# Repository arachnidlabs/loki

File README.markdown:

Loki
====

Loki is a flexible development platform based on Cypress's PSoC 5 line of processors.

For much more about Loki, check out the [Arachnid Labs Blog](http://www.arachnidlabs.com/)

All the Loki source and schematics are open hardware and OSS, and licensed under the [BSD 2-clause license](http://opensource.org/licenses/BSD-2-Clause). Reuse and remix as you see fit!

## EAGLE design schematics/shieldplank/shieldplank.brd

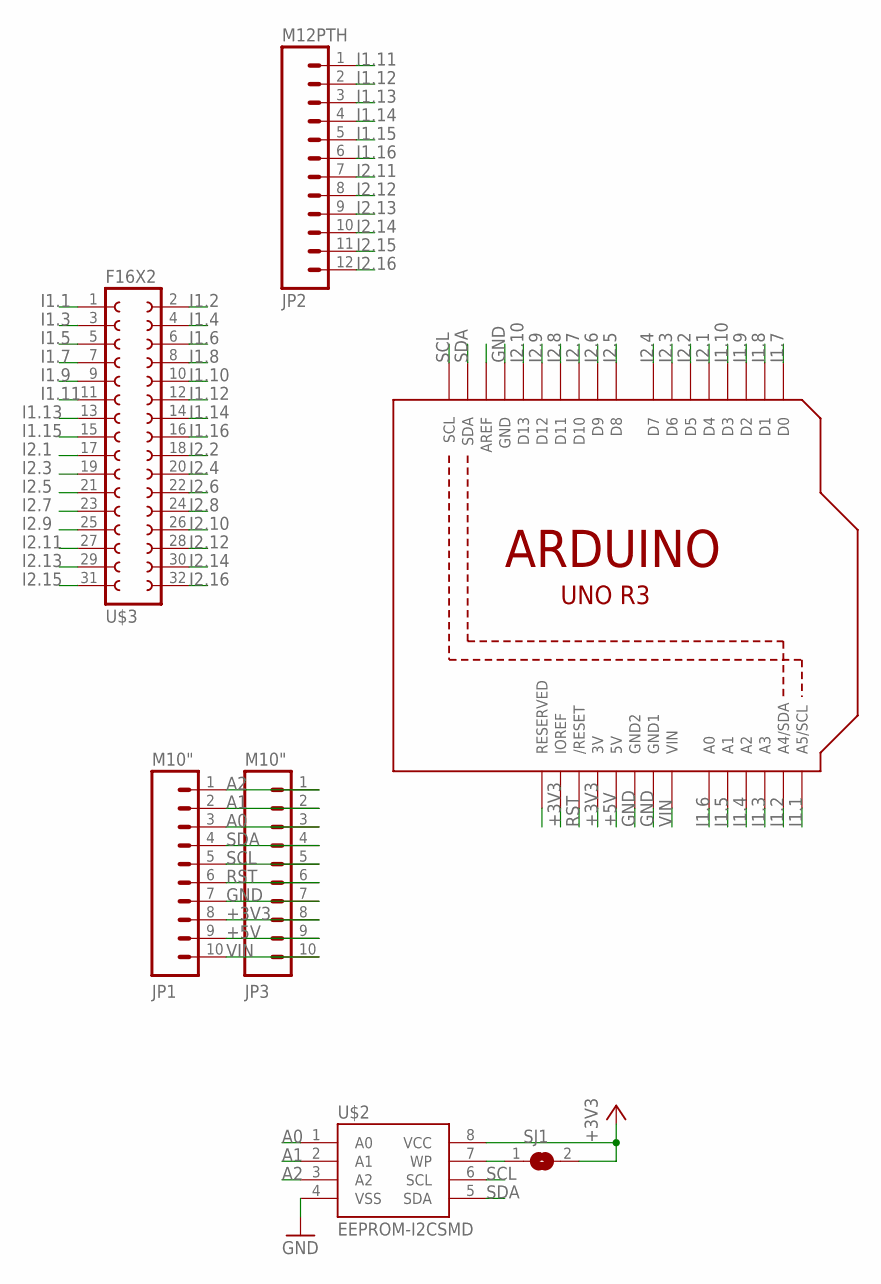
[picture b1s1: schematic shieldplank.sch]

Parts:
JP1, JP3: M10"; 1X10
JP2: M12PTH; 1X12
SJ1: SJ
U1: ARDUINOR3-BPLACE
U$2: EEPROM-I2CSMD; SO08
U$3: F16X2; FE16-2

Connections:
+3V3: JP1.8, JP3.8, SJ1.2, U1.3V, U1.IOREF, U$2.8 (VCC)
+5V: JP1.9, JP3.9, U1.5V
A0: JP1.3, JP3.3, U$2.1 (A0)
A1: JP1.2, JP3.2, U$2.2 (A1)
A2: JP1.1, JP3.1, U$2.3 (A2)
GND: JP1.7, JP3.7, U1.GND, U1.GND1, U1.GND2, U$2.4 (VSS)
I1.1: U1.A5 (A5/SCL), U$3.1
I1.2: U1.A4 (A4/SDA), U$3.2
I1.3: U1.A3, U$3.3
I1.4: U1.A2, U$3.4
I1.5: U1.A1, U$3.5
I1.6: U1.A0, U$3.6
I1.7: U1.D0, U$3.7
I1.8: U1.D1, U$3.8
I1.9: U1.D2, U$3.9
I1.10: U1.D3, U$3.10
I1.11: JP2.1, U$3.11
I1.12: JP2.2, U$3.12
I1.13: JP2.3, U$3.13
I1.14: JP2.4, U$3.14
I1.15: JP2.5, U$3.15
I1.16: JP2.6, U$3.16
I2.1: U1.D4, U$3.17
I2.2: U1.D5, U$3.18
I2.3: U1.D6, U$3.19
I2.4: U1.D7, U$3.20
I2.5: U1.D8, U$3.21
I2.6: U1.D9, U$3.22
I2.7: U1.D10, U$3.23
I2.8: U1.D11, U$3.24
I2.9: U1.D12, U$3.25
I2.10: U1.D13, U$3.26
I2.11: JP2.7, U$3.27
I2.12: JP2.8, U$3.28
I2.13: JP2.9, U$3.29
I2.14: JP2.10, U$3.30
I2.15: JP2.11, U$3.31
I2.16: JP2.12, U$3.32
unnamed: SJ1.1, U$2.7 (WP)
RST: JP1.6, JP3.6, U1.RESET (/RESET)
SCL: JP1.5, JP3.5, U1.SCL, U$2.6 (SCL)
SDA: JP1.4, JP3.4, U1.SDA, U$2.5 (SDA)
VIN: JP1.10, JP3.10, U1.VIN

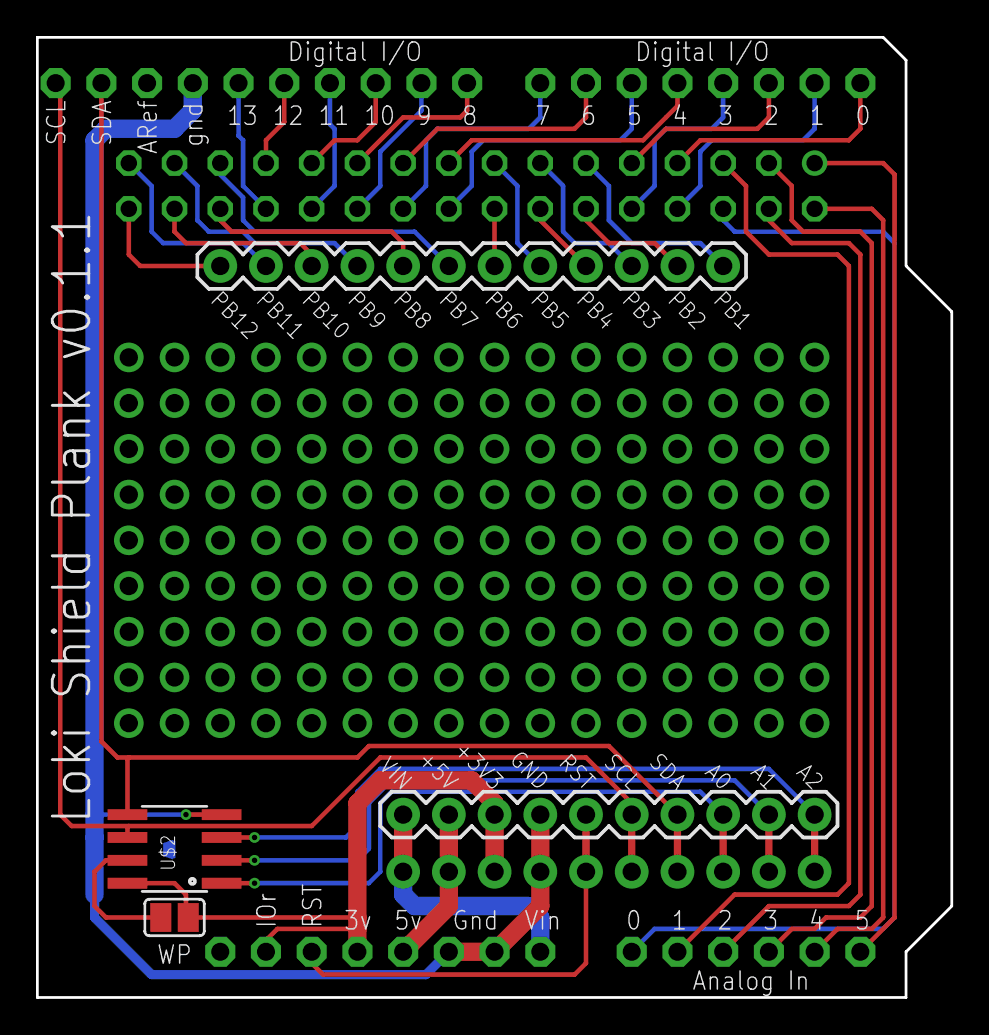
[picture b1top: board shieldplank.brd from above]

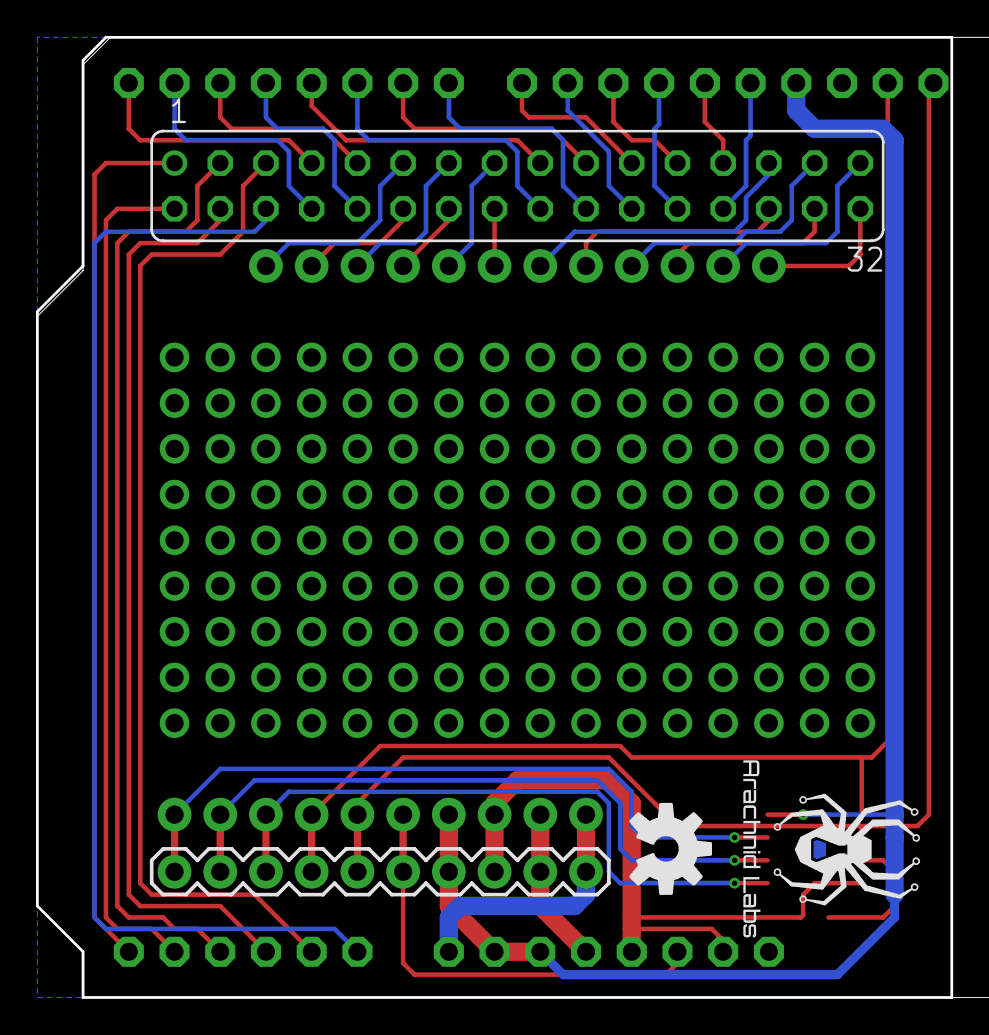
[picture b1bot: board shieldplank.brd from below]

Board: 2 copper layers, 50.8 x 53.3 mm, 9 parts (4 on the bottom side), 43 nets.

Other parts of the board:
U$1: ARACHNID_LABS_LOGO_SM
U$4: OSHW-LOGO-M

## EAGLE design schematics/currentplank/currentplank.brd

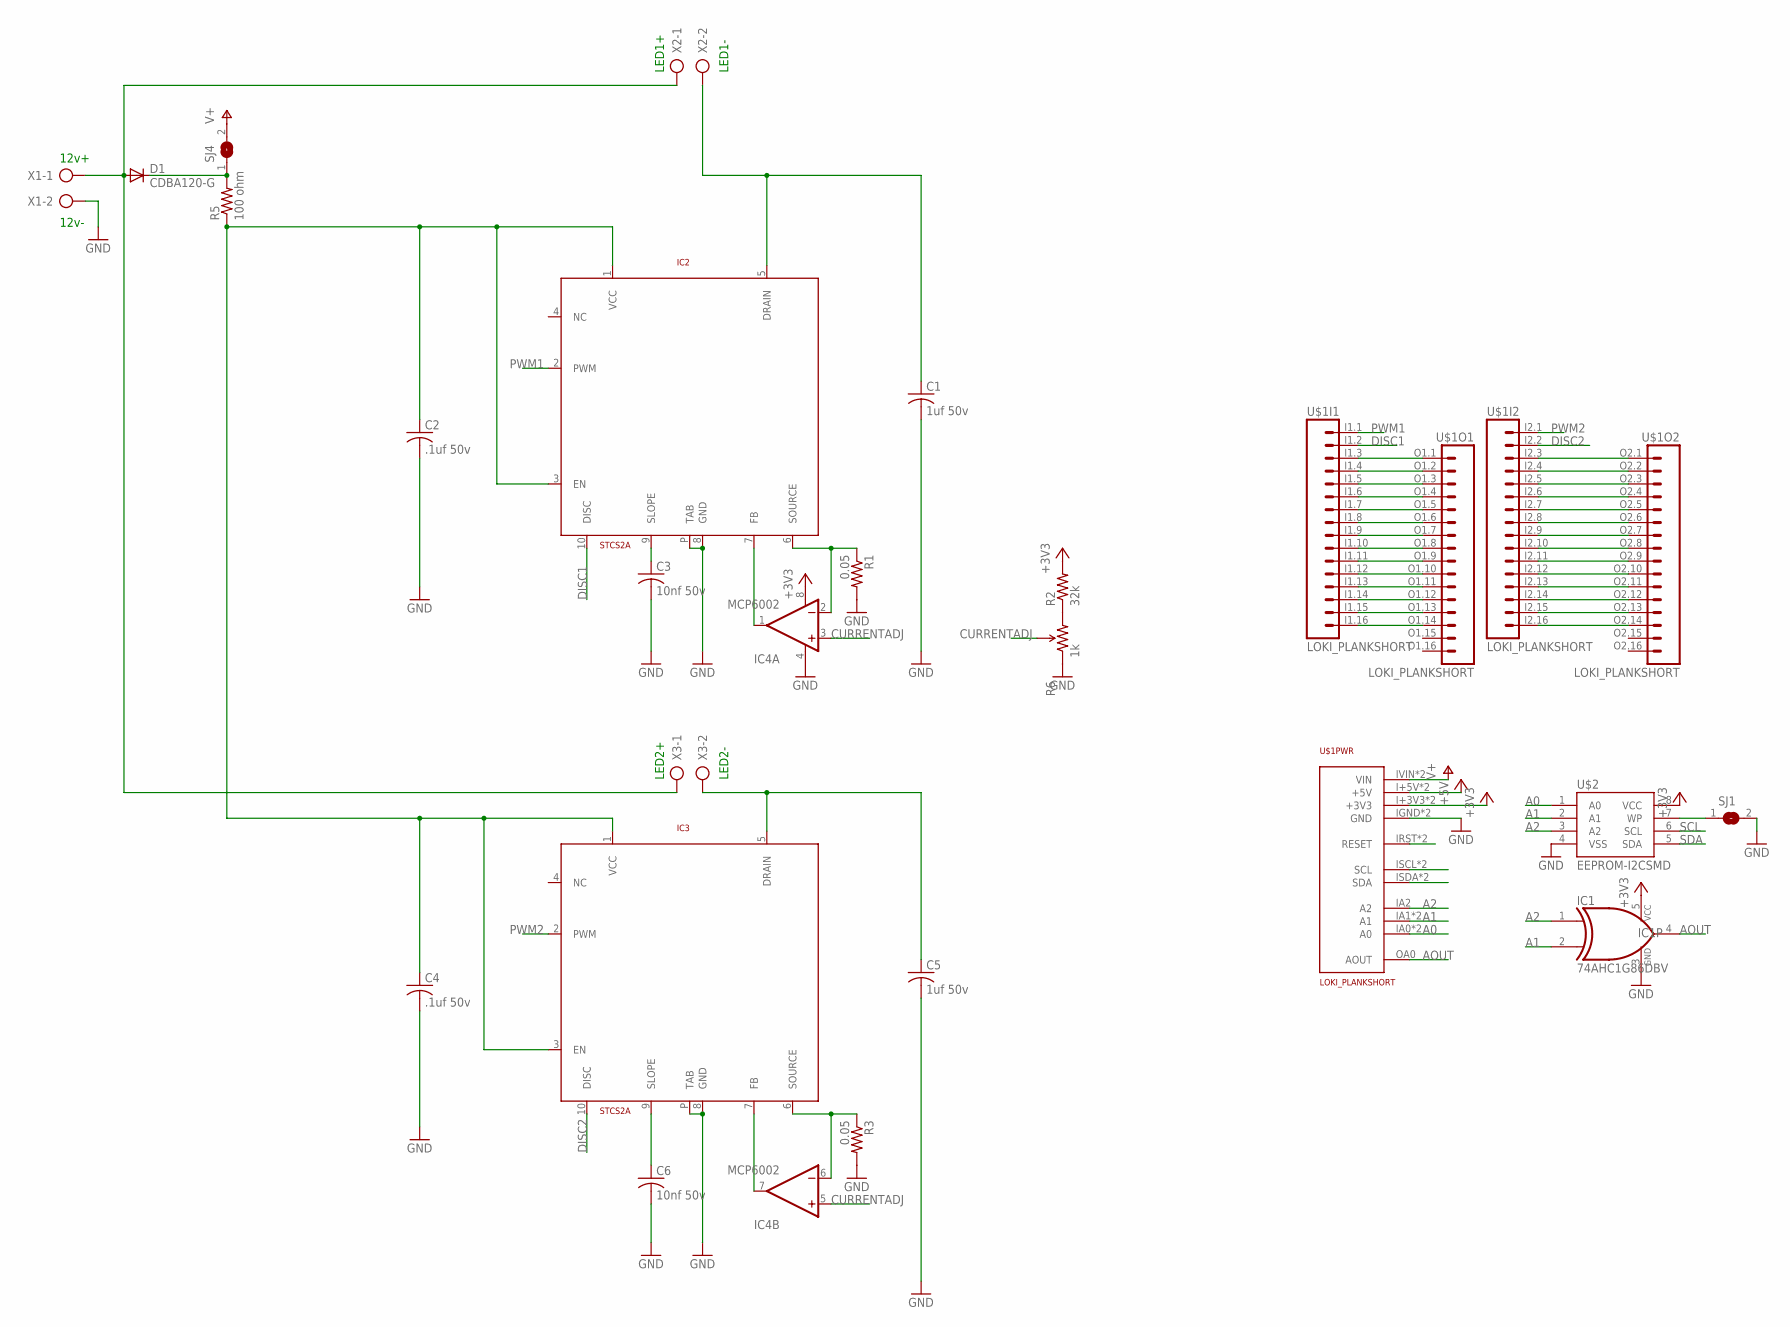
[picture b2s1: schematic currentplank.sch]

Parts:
C1, C5: 1uf 50v; C0805
C2, C4: .1uf 50v; C0805
C3, C6: 10nf 50v; C0805
D1: CDBA120-G; SMA-DIODE
IC1: 74AHC1G86DBV; SOT23-5
IC2, IC3: STCS2A; STCS2A_POWER-SO10
IC4: MCP6002; SO08
R1, R3: 0.05; 1206
R2: 32k; 0805
R5: 100 ohm; 0805
R6: 1k; TRIMPOT-3MM-2
SJ1, SJ4: SJ
U$1: LOKI_PLANKSHORT; PLANK_SHORT
U$2: EEPROM-I2CSMD; SO08
X1, X2, X3: AK500/2-H

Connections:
+3V3: IC1.5 (VCC), IC4.8 (V+), R2.2, U$1.I+3V3 (+3V3), U$1.O+3V3 (+3V3), U$2.8 (VCC)
+5V: U$1.I+5V (+5V), U$1.O+5V (+5V)
A0: U$1.IA0 (A0), U$1.OA1 (A0), U$2.1 (A0)
A1: IC1.2 (I1), U$1.IA1 (A1), U$1.OA2 (A1), U$2.2 (A1)
A2: IC1.1 (I0), U$1.IA2 (A2), U$2.3 (A2)
AOUT: IC1.4 (O), U$1.OA0 (AOUT)
CURRENTADJ: IC4.3 (+IN), IC4.5 (+IN), R6.2 (WIPER)
DISC1: IC2.10 (DISC), U$1.I1.2 (2)
DISC2: IC3.10 (DISC), U$1.I2.2 (2)
GND: C1.2, C2.2, C3.2, C4.2, C5.2, C6.2, IC1.3 (GND), IC2.8 (GND), IC2.P (TAB), IC3.8 (GND), IC3.P (TAB), IC4.4 (V-), R1.2, R3.2, R6.1 (CCW), SJ1.2, U$1.IGND (GND), U$1.OGND (GND), U$2.4 (VSS), X1.2
unnamed: U$1.I1.16 (16), U$1.O1.14 (14)
unnamed: U$1.I1.15 (15), U$1.O1.13 (13)
unnamed: U$1.I1.14 (14), U$1.O1.12 (12)
unnamed: U$1.I1.13 (13), U$1.O1.11 (11)
unnamed: U$1.I1.12 (12), U$1.O1.10 (10)
unnamed: U$1.I1.11 (11), U$1.O1.9 (9)
unnamed: U$1.I1.10 (10), U$1.O1.8 (8)
unnamed: U$1.I1.9 (9), U$1.O1.7 (7)
unnamed: U$1.I1.8 (8), U$1.O1.6 (6)
unnamed: U$1.I1.7 (7), U$1.O1.5 (5)
unnamed: U$1.I1.6 (6), U$1.O1.4 (4)
unnamed: U$1.I1.5 (5), U$1.O1.3 (3)
unnamed: U$1.I1.4 (4), U$1.O1.2 (2)
unnamed: U$1.I1.3 (3), U$1.O1.1 (1)
unnamed: U$1.I2.16 (16), U$1.O2.14 (14)
unnamed: U$1.I2.15 (15), U$1.O2.13 (13)
unnamed: U$1.I2.14 (14), U$1.O2.12 (12)
unnamed: U$1.I2.13 (13), U$1.O2.11 (11)
unnamed: U$1.I2.12 (12), U$1.O2.10 (10)
unnamed: U$1.I2.11 (11), U$1.O2.9 (9)
unnamed: U$1.I2.10 (10), U$1.O2.8 (8)
unnamed: U$1.I2.9 (9), U$1.O2.7 (7)
unnamed: U$1.I2.8 (8), U$1.O2.6 (6)
unnamed: U$1.I2.7 (7), U$1.O2.5 (5)
unnamed: U$1.I2.6 (6), U$1.O2.4 (4)
unnamed: U$1.I2.5 (5), U$1.O2.3 (3)
unnamed: U$1.I2.4 (4), U$1.O2.2 (2)
unnamed: U$1.I2.3 (3), U$1.O2.1 (1)
unnamed: IC2.6 (SOURCE), IC4.2 (-IN), R1.1
unnamed: IC2.7 (FB), IC4.1 (OUT)
unnamed: SJ1.1, U$2.7 (WP)
unnamed: U$1.IRST (RESET), U$1.ORST (RESET)
unnamed: D1.C, R5.2, SJ4.1
unnamed: C3.1, IC2.9 (SLOPE)
unnamed: D1.A, X1.1, X2.1, X3.1
unnamed: C1.1, IC2.5 (DRAIN), X2.2
unnamed: C5.1, IC3.5 (DRAIN), X3.2
unnamed: C6.1, IC3.9 (SLOPE)
unnamed: IC3.6 (SOURCE), IC4.6 (-IN), R3.1
unnamed: IC3.7 (FB), IC4.7 (OUT)
unnamed: R2.1, R6.3 (CW)
unnamed: C2.1, C4.1, IC2.1 (VCC), IC2.3 (EN), IC3.1 (VCC), IC3.3 (EN), R5.1
PWM1: IC2.2 (PWM), U$1.I1.1 (1)
PWM2: IC3.2 (PWM), U$1.I2.1 (1)
SCL: U$1.ISCL (SCL), U$1.OSCL (SCL), U$2.6 (SCL)
SDA: U$1.ISDA (SDA), U$1.OSDA (SDA), U$2.5 (SDA)
V+: SJ4.2, U$1.IVIN (VIN), U$1.OVIN (VIN)

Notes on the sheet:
12v+
12v-
LED1+
LED1-
LED2-
LED2+

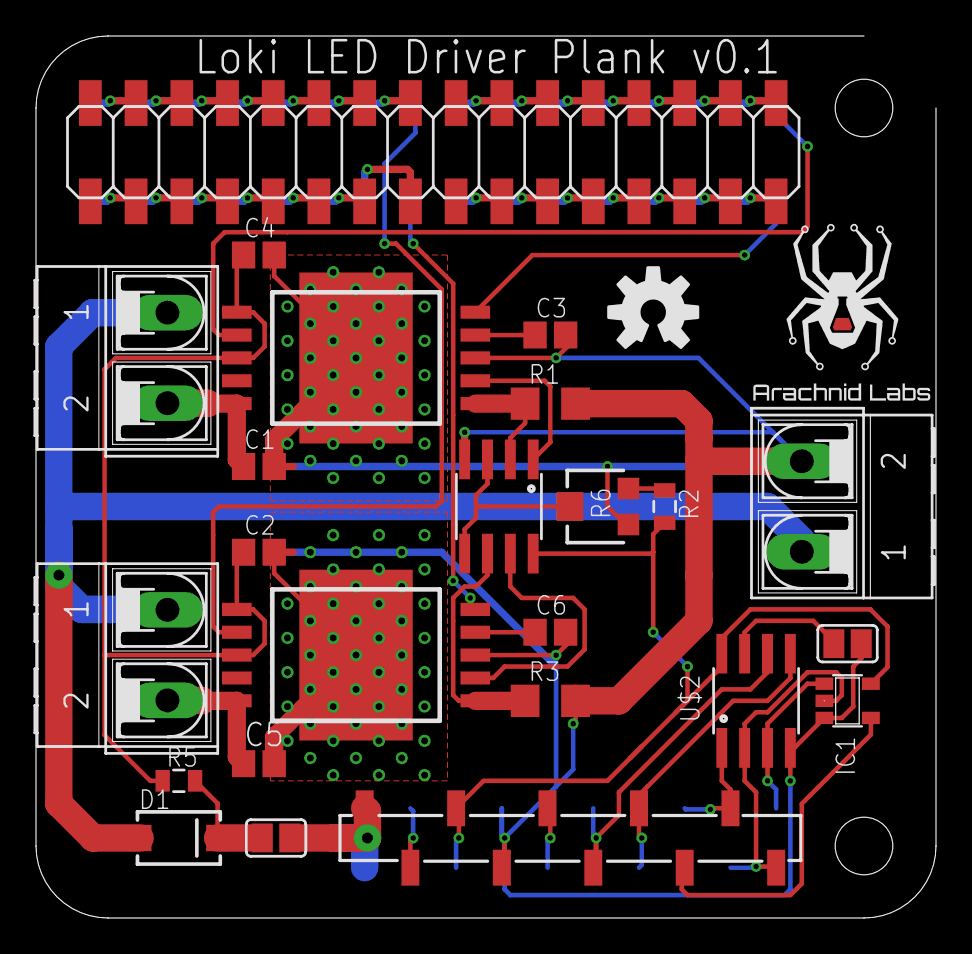
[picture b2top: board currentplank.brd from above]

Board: 2 copper layers, 50.0 x 49.0 mm, 25 parts (0 on the bottom side), 57 nets.

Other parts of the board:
U$3: OSHW-LOGO-M
U$4: ARACHNID_LABS_LOGO_SM

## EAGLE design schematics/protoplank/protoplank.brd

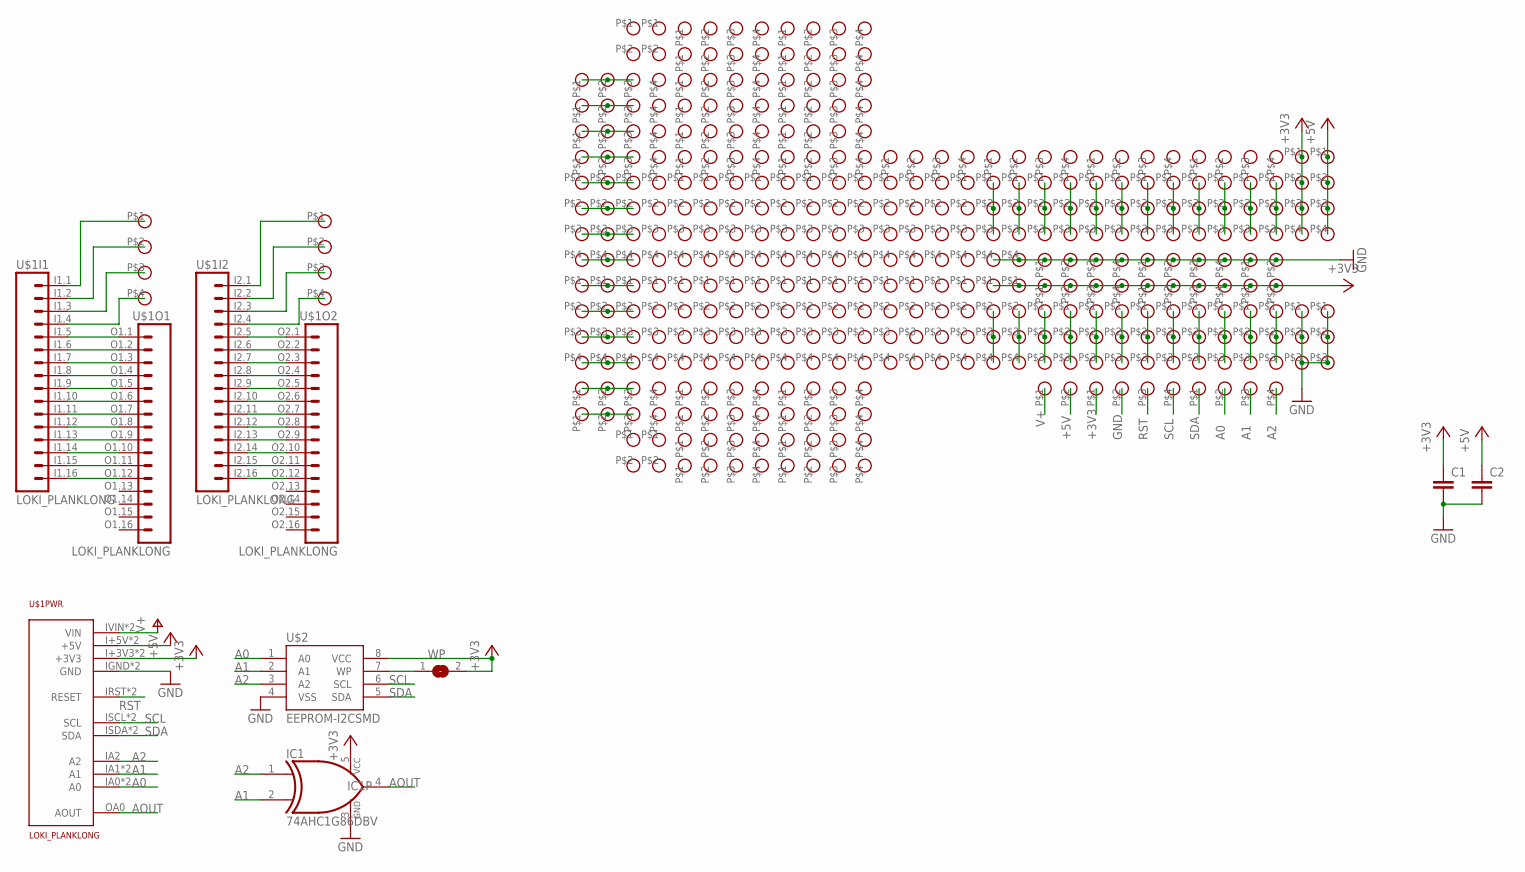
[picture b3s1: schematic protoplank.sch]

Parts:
C1, C2: CAPPTH; CAP-PTH-SMALL
IC1: 74AHC1G86DBV; SOT23-5
U$1: LOKI_PLANKLONG; PLANK_LONG
U$2: EEPROM-I2CSMD; SO08
U$3, U$4, U$5, U$6, U$7, U$8, U$9, U$10, U$11, U$12, U$13, U$14, U$15, U$16, U$17, U$18, U$19, U$20, U$21, U$22, U$78, U$80: PROTOPAD-3
U$23, U$24, U$25, U$26, U$34, U$35, U$36, U$37, U$38, U$39, U$40, U$41, U$42, U$43, U$44, U$45, U$46, U$47, U$48, U$49, U$50, U$51, U$52, U$53, U$54, U$55, U$56, U$57, U$58, U$59, U$60, U$61, U$62, U$63, U$64, U$65, U$66, U$67, U$68, U$69, U$70, U$71, U$72, U$73, U$74, U$75, U$76, U$77, U$79, U$81, U$82, U$83, U$84, U$85, U$86, U$87, U$88, U$89, U$90, U$91, U$92, U$93, U$94, U$95, U$96, U$97, U$98, U$99, U$100, U$101, U$102, U$103: PROTOPAD-4SQUARE; PROTOPAD-4
U$27, U$28, U$104, U$105, U$106, U$107: PROTOPAD-2SQUARE; PROTOPAD-2
U$29, U$30, U$31, U$32: PROTOPAD-4ROUND; PROTOPAD-4-ROUND
U$33: PROTOPAD-2ROUND; PROTOPAD-2-ROUND
WP: SJ

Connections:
+3V3: C1.1, IC1.5 (VCC), U$1.I+3V3 (+3V3), U$1.O+3V3 (+3V3), U$2.8 (VCC), U$25.P$1, U$25.P$2, U$25.P$3, U$25.P$4, U$26.P$1, U$26.P$2, U$26.P$3, U$26.P$4, U$28.P$1, U$28.P$2, U$32.P$1, U$35.P$1, U$36.P$1, U$77.P$1, U$77.P$2, U$77.P$3, U$77.P$4, WP.2
+5V: C2.1, U$1.I+5V (+5V), U$1.O+5V (+5V), U$33.P$2, U$79.P$1, U$79.P$2, U$79.P$3, U$79.P$4
A0: U$1.IA0 (A0), U$1.OA1 (A0), U$2.1 (A0), U$31.P$2
A1: IC1.2 (I1), U$1.IA1 (A1), U$1.OA2 (A1), U$2.2 (A1), U$31.P$3
A2: IC1.1 (I0), U$1.IA2 (A2), U$2.3 (A2), U$31.P$4
AOUT: IC1.4 (O), U$1.OA0 (AOUT)
GND: C1.2, C2.2, IC1.3 (GND), U$1.IGND (GND), U$1.OGND (GND), U$2.4 (VSS), U$23.P$1, U$23.P$2, U$23.P$3, U$23.P$4, U$24.P$1, U$24.P$2, U$24.P$3, U$24.P$4, U$27.P$1, U$27.P$2, U$32.P$2, U$34.P$4, U$37.P$4, U$78.P$1, U$78.P$2, U$78.P$3, U$80.P$1, U$80.P$2, U$80.P$3
unnamed: U$1.I1.16 (16), U$1.O1.12 (12)
unnamed: U$1.I1.15 (15), U$1.O1.11 (11)
unnamed: U$1.I1.14 (14), U$1.O1.10 (10)
unnamed: U$1.I1.13 (13), U$1.O1.9 (9)
unnamed: U$1.I1.12 (12), U$1.O1.8 (8)
unnamed: U$1.I1.11 (11), U$1.O1.7 (7)
unnamed: U$1.I1.10 (10), U$1.O1.6 (6)
unnamed: U$1.I1.9 (9), U$1.O1.5 (5)
unnamed: U$1.I1.8 (8), U$1.O1.4 (4)
unnamed: U$1.I1.7 (7), U$1.O1.3 (3)
unnamed: U$1.I1.6 (6), U$1.O1.2 (2)
unnamed: U$1.I1.5 (5), U$1.O1.1 (1)
unnamed: U$1.I2.16 (16), U$1.O2.12 (12)
unnamed: U$1.I2.15 (15), U$1.O2.11 (11)
unnamed: U$1.I2.14 (14), U$1.O2.10 (10)
unnamed: U$1.I2.13 (13), U$1.O2.9 (9)
unnamed: U$1.I2.12 (12), U$1.O2.8 (8)
unnamed: U$1.I2.11 (11), U$1.O2.7 (7)
unnamed: U$1.I2.10 (10), U$1.O2.6 (6)
unnamed: U$1.I2.9 (9), U$1.O2.5 (5)
unnamed: U$1.I2.8 (8), U$1.O2.4 (4)
unnamed: U$1.I2.7 (7), U$1.O2.3 (3)
unnamed: U$1.I2.6 (6), U$1.O2.2 (2)
unnamed: U$1.I2.5 (5), U$1.O2.1 (1)
unnamed: U$1.I1.4 (4), U$29.P$4
unnamed: U$1.I1.3 (3), U$29.P$3
unnamed: U$1.I1.2 (2), U$29.P$2
unnamed: U$1.I1.1 (1), U$29.P$1
unnamed: U$1.I2.4 (4), U$30.P$4
unnamed: U$1.I2.3 (3), U$30.P$3
unnamed: U$2.7 (WP), WP.1
unnamed: U$3.P$1, U$3.P$2, U$3.P$3
unnamed: U$1.I2.2 (2), U$30.P$2
unnamed: U$1.I2.1 (1), U$30.P$1
unnamed: U$4.P$1, U$4.P$2, U$4.P$3
unnamed: U$5.P$1, U$5.P$2, U$5.P$3
unnamed: U$6.P$1, U$6.P$2, U$6.P$3
unnamed: U$7.P$1, U$7.P$2, U$7.P$3
unnamed: U$8.P$1, U$8.P$2, U$8.P$3
unnamed: U$9.P$1, U$9.P$2, U$9.P$3
unnamed: U$10.P$1, U$10.P$2, U$10.P$3
unnamed: U$11.P$1, U$11.P$2, U$11.P$3
unnamed: U$12.P$1, U$12.P$2, U$12.P$3
unnamed: U$13.P$1, U$13.P$2, U$13.P$3
unnamed: U$14.P$1, U$14.P$2, U$14.P$3
unnamed: U$15.P$1, U$15.P$2, U$15.P$3
unnamed: U$16.P$1, U$16.P$2, U$16.P$3
unnamed: U$17.P$1, U$17.P$2, U$17.P$3
unnamed: U$18.P$1, U$18.P$2, U$18.P$3
unnamed: U$19.P$1, U$19.P$2, U$19.P$3
unnamed: U$20.P$1, U$20.P$2, U$20.P$3
unnamed: U$21.P$1, U$21.P$2, U$21.P$3
unnamed: U$22.P$1, U$22.P$2, U$22.P$3
unnamed: U$89.P$1, U$89.P$2, U$89.P$3
unnamed: U$88.P$1, U$88.P$2, U$88.P$3
unnamed: U$34.P$1, U$34.P$2, U$34.P$3
unnamed: U$37.P$1, U$37.P$2, U$37.P$3
unnamed: U$81.P$1, U$81.P$2, U$81.P$3
unnamed: U$35.P$2, U$35.P$3, U$35.P$4
unnamed: U$36.P$2, U$36.P$3, U$36.P$4
unnamed: U$76.P$1, U$76.P$2, U$76.P$3
unnamed: U$65.P$1, U$66.P$1, U$69.P$1
unnamed: U$65.P$2, U$66.P$2, U$69.P$2
unnamed: U$65.P$3, U$66.P$3, U$69.P$3
unnamed: U$65.P$4, U$66.P$4, U$69.P$4
unnamed: U$64.P$1, U$67.P$1, U$68.P$1
unnamed: U$64.P$2, U$67.P$2, U$68.P$2
unnamed: U$64.P$3, U$67.P$3, U$68.P$3
unnamed: U$64.P$4, U$67.P$4, U$68.P$4
unnamed: U$96.P$1, U$96.P$2, U$96.P$3
unnamed: U$99.P$1, U$99.P$2, U$99.P$3
RST: U$1.IRST (RESET), U$1.ORST (RESET), U$32.P$3
SCL: U$1.ISCL (SCL), U$1.OSCL (SCL), U$2.6 (SCL), U$32.P$4
SDA: U$1.ISDA (SDA), U$1.OSDA (SDA), U$2.5 (SDA), U$31.P$1
V+: U$1.IVIN (VIN), U$1.OVIN (VIN), U$33.P$1

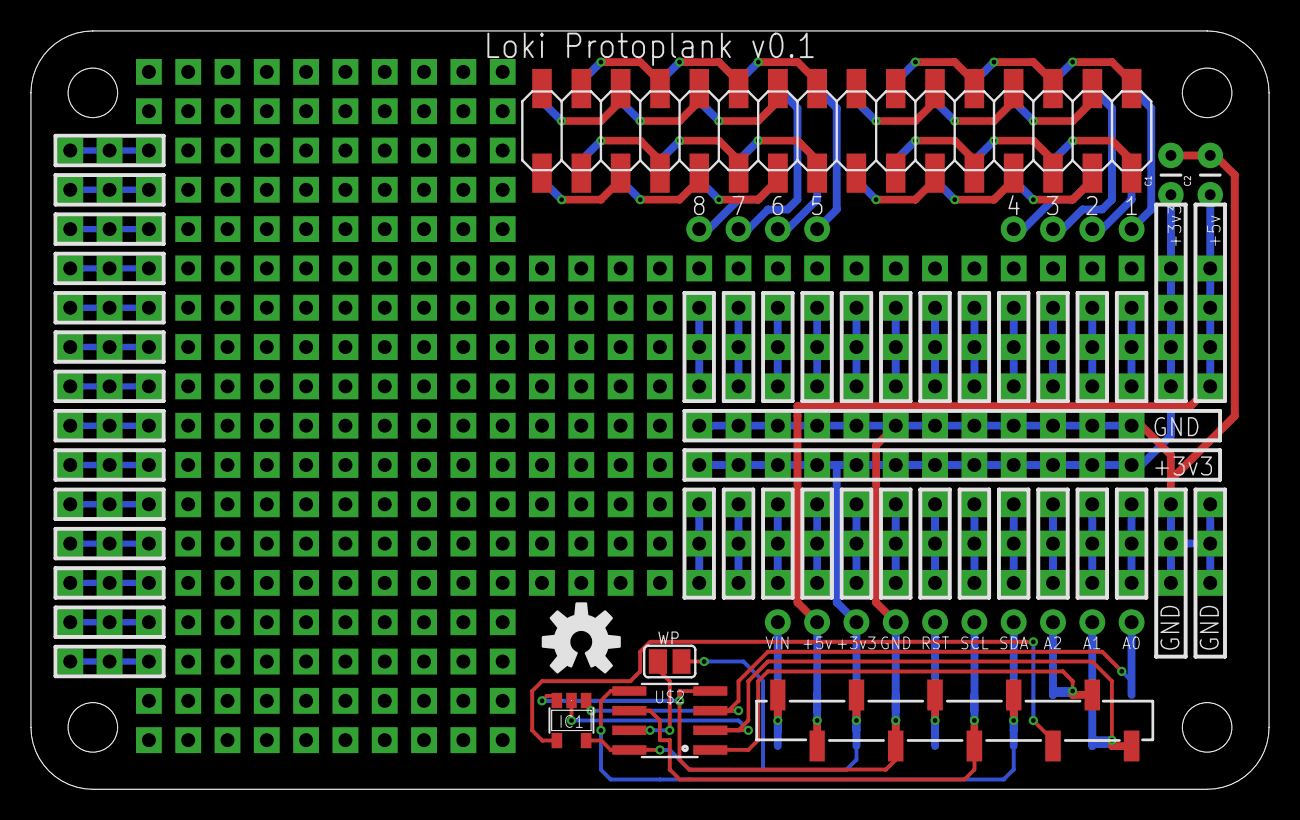
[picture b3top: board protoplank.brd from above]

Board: 2 copper layers, 80.0 x 49.0 mm, 112 parts (0 on the bottom side), 82 nets.

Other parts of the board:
U$108: OSHW-LOGO-M

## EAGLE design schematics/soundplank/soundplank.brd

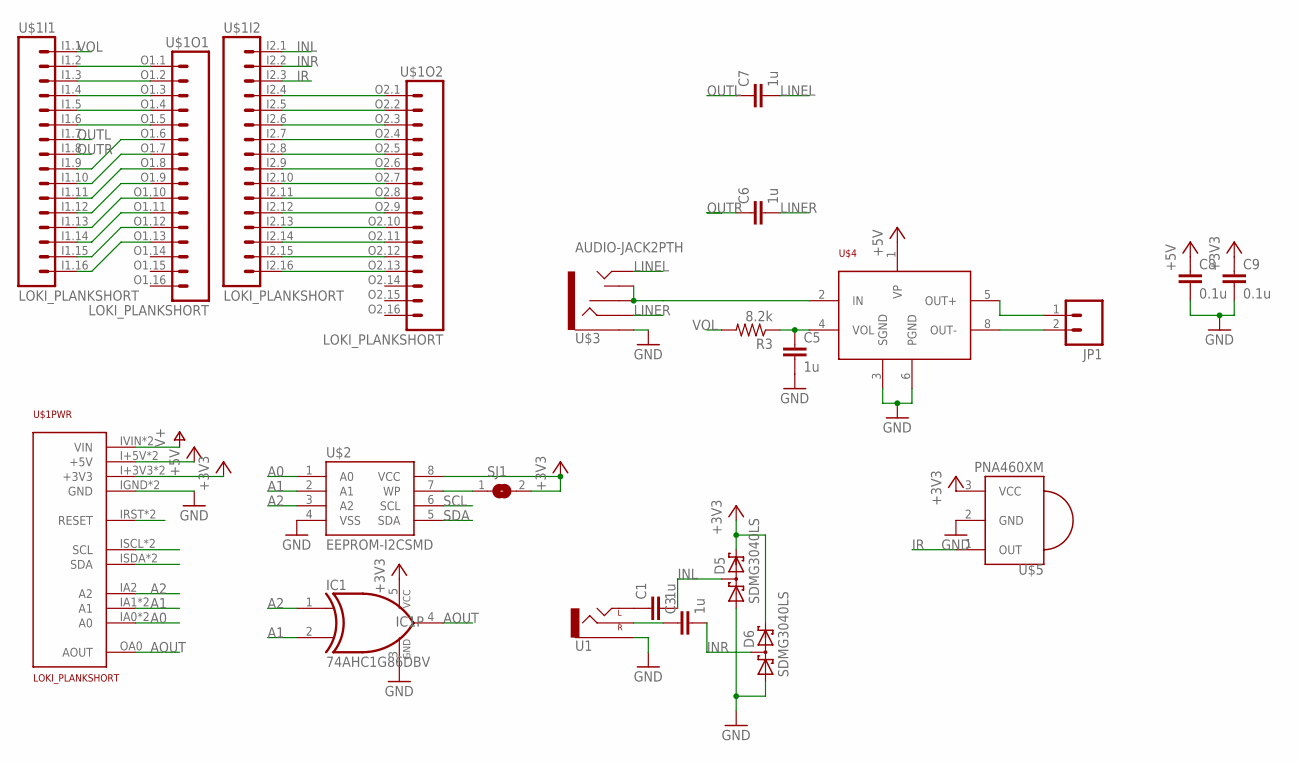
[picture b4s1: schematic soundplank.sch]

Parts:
C1, C3, C6, C7: 1u; 1210
C5: 1u; 0805
C8, C9: 0.1u; 0805
D5, D6: SDMG3040LS; SOT23
IC1: 74AHC1G86DBV; SOT23-5
JP1: M023.5MM; SCREWTERMINAL-3.5MM-2
R3: 8.2k; 0805
SJ1: SJ
U1: AUDIO-JACKPTH; AUDIO-JACK
U$1: LOKI_PLANKSHORT; PLANK_SHORT
U$2: EEPROM-I2CSMD; SO08
U$3: AUDIO-JACK2PTH; AUDIO-JACK
U$4: TDA7052A; SO08-MAX6675
U$5: PNA460XM

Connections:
+3V3: C9.1, D5.2 (C2), D6.2 (C2), IC1.5 (VCC), SJ1.2, U$1.I+3V3 (+3V3), U$1.O+3V3 (+3V3), U$2.8 (VCC), U$5.3 (VCC)
+5V: C8.1, U$1.I+5V (+5V), U$1.O+5V (+5V), U$4.1 (VP)
A0: U$1.IA0 (A0), U$1.OA1 (A0), U$2.1 (A0)
A1: IC1.2 (I1), U$1.IA1 (A1), U$1.OA2 (A1), U$2.2 (A1)
A2: IC1.1 (I0), U$1.IA2 (A2), U$2.3 (A2)
AOUT: IC1.4 (O), U$1.OA0 (AOUT)
GND: C5.2, C8.2, C9.2, D5.1 (A1), D6.1 (A1), IC1.3 (GND), U1.SLEEVE, U$1.IGND (GND), U$1.OGND (GND), U$2.4 (VSS), U$3.SLEEVE, U$4.3 (SGND), U$4.6 (PGND), U$5.2 (GND)
INL: C1.2, D5.3 (C1A2), U$1.I2.1 (1)
INR: C3.2, D6.3 (C1A2), U$1.I2.2 (2)
IR: U$1.I2.3 (3), U$5.1 (OUT)
LINEL: C7.2, U$3.TIP
LINER: C6.2, U$3.RING
unnamed: U$1.I1.2 (2), U$1.O1.1 (1)
unnamed: U$1.I1.3 (3), U$1.O1.2 (2)
unnamed: U$1.I1.4 (4), U$1.O1.3 (3)
unnamed: U$1.I1.5 (5), U$1.O1.4 (4)
unnamed: U$1.I1.6 (6), U$1.O1.5 (5)
unnamed: U$1.I1.9 (9), U$1.O1.6 (6)
unnamed: U$1.I1.10 (10), U$1.O1.7 (7)
unnamed: U$1.I1.11 (11), U$1.O1.8 (8)
unnamed: U$1.I1.12 (12), U$1.O1.9 (9)
unnamed: U$1.I1.13 (13), U$1.O1.10 (10)
unnamed: U$1.I1.14 (14), U$1.O1.11 (11)
unnamed: U$1.I1.15 (15), U$1.O1.12 (12)
unnamed: U$1.I1.16 (16), U$1.O1.13 (13)
unnamed: U$1.I2.16 (16), U$1.O2.13 (13)
unnamed: U$1.I2.15 (15), U$1.O2.12 (12)
unnamed: U$1.I2.14 (14), U$1.O2.11 (11)
unnamed: U$1.I2.13 (13), U$1.O2.10 (10)
unnamed: U$1.I2.12 (12), U$1.O2.9 (9)
unnamed: U$1.I2.11 (11), U$1.O2.8 (8)
unnamed: U$1.I2.10 (10), U$1.O2.7 (7)
unnamed: U$1.I2.9 (9), U$1.O2.6 (6)
unnamed: U$1.I2.8 (8), U$1.O2.5 (5)
unnamed: U$1.I2.7 (7), U$1.O2.4 (4)
unnamed: U$1.I2.6 (6), U$1.O2.3 (3)
unnamed: U$1.I2.5 (5), U$1.O2.2 (2)
unnamed: U$1.I2.4 (4), U$1.O2.1 (1)
unnamed: C5.1, R3.1, U$4.4 (VOL)
unnamed: JP1.2, U$4.8 (OUT-)
unnamed: SJ1.1, U$2.7 (WP)
unnamed: U$1.IRST (RESET), U$1.ORST (RESET)
unnamed: JP1.1, U$4.5 (OUT+)
unnamed: C1.1, U1.TIP (LEFT)
unnamed: U$3.RSH, U$3.TSH, U$4.2 (IN)
unnamed: C3.1, U1.RING (RIGHT)
OUTL: C7.1, U$1.I1.7 (7)
OUTR: C6.1, U$1.I1.8 (8)
SCL: U$1.ISCL (SCL), U$1.OSCL (SCL), U$2.6 (SCL)
SDA: U$1.ISDA (SDA), U$1.OSDA (SDA), U$2.5 (SDA)
V+: U$1.IVIN (VIN), U$1.OVIN (VIN)
VOL: R3.2, U$1.I1.1 (1)

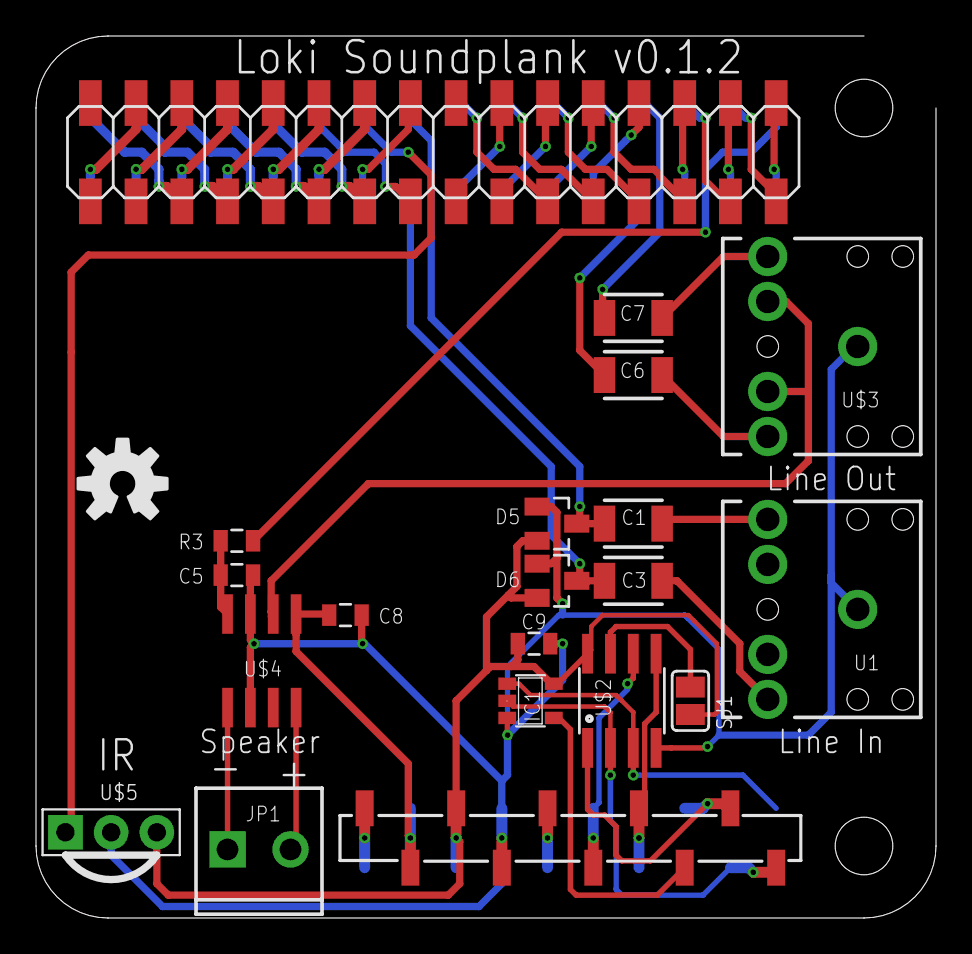
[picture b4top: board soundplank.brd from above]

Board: 2 copper layers, 50.0 x 49.0 mm, 20 parts (0 on the bottom side), 52 nets.

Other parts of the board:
U$6: OSHW-LOGO-M

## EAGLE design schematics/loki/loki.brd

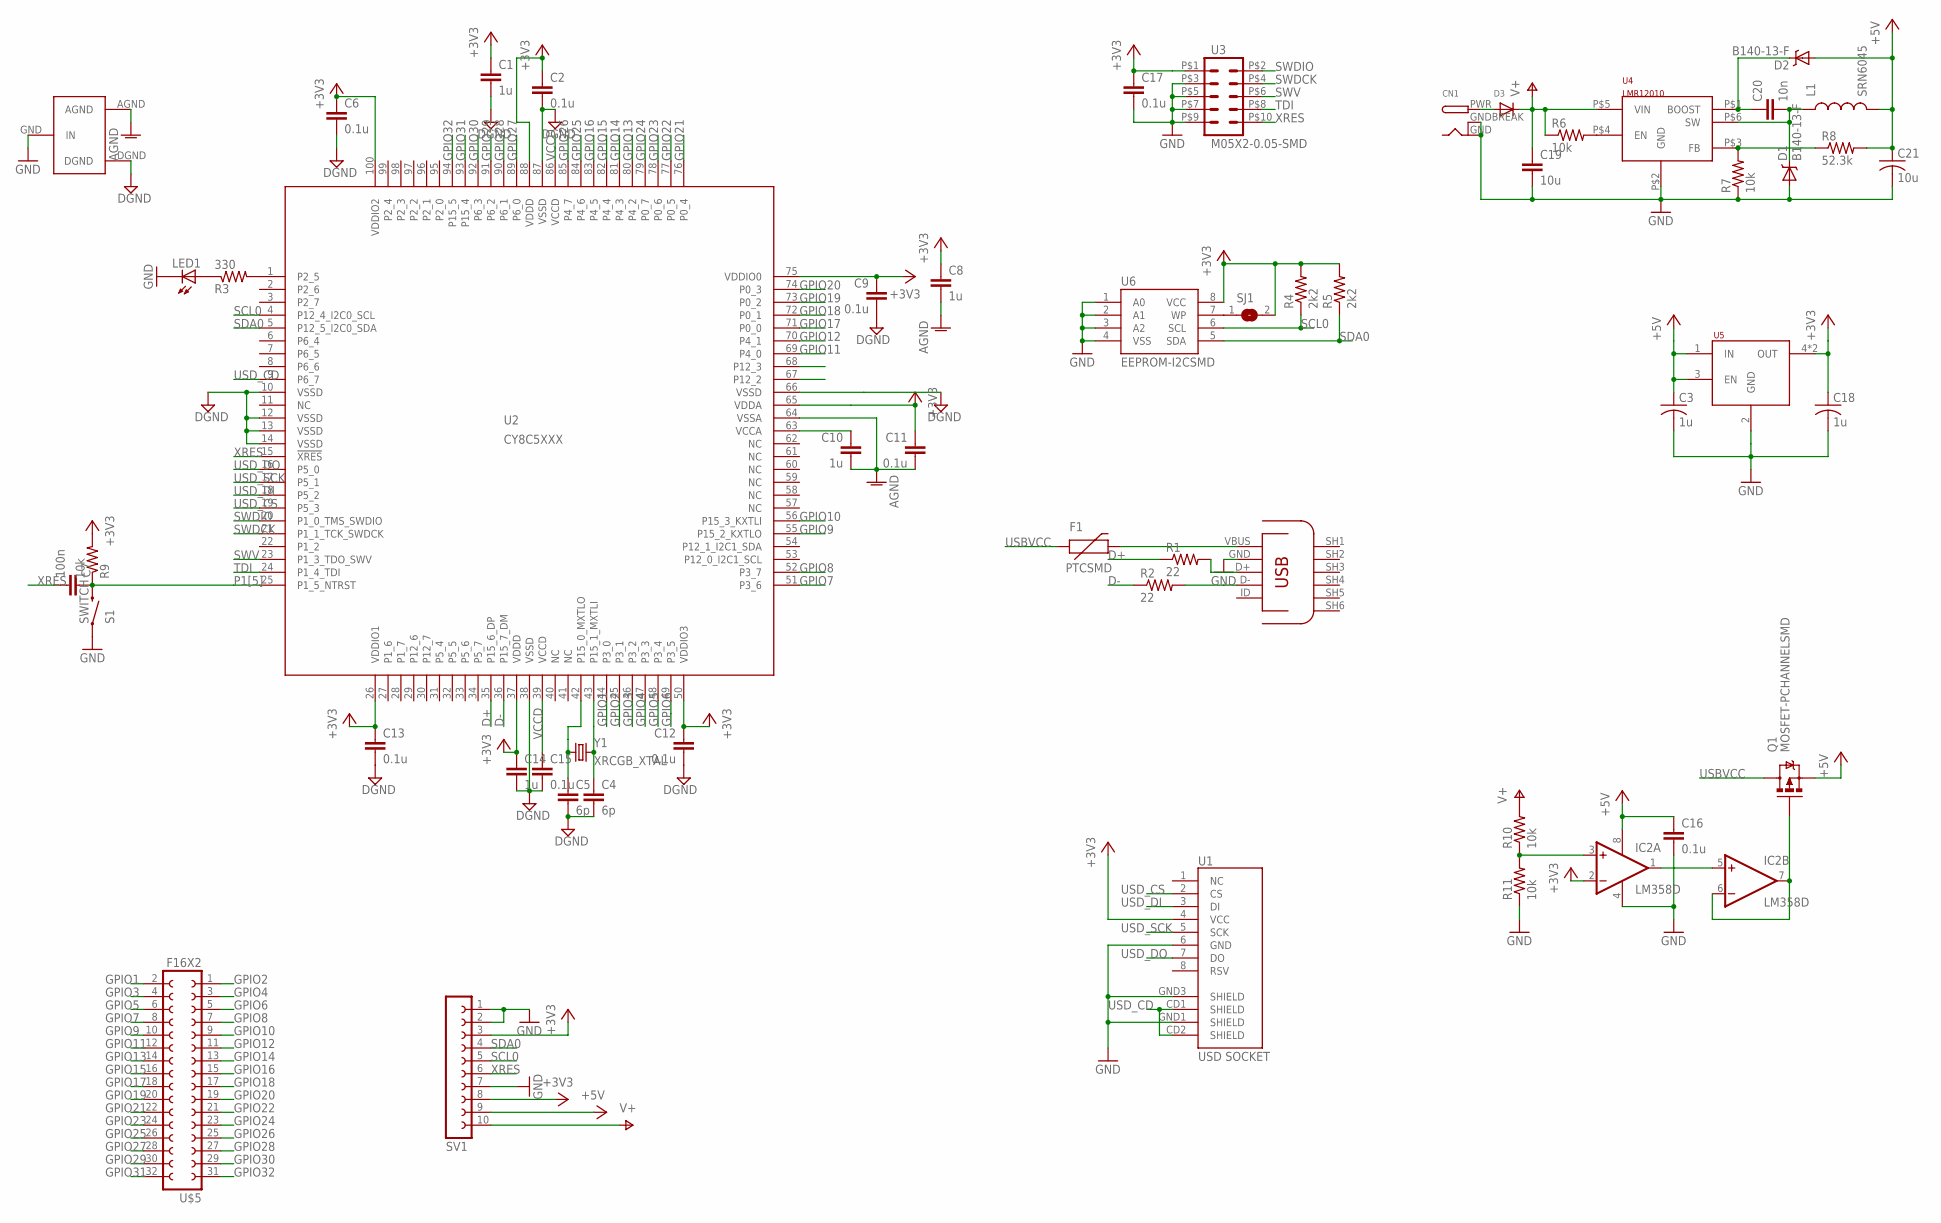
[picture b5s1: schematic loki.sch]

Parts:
C1, C8, C10, C14: 1u; C0603K
C2, C6, C9, C11, C12, C13, C15, C17: 0.1u; C0603K
C3, C18: 1u; C0603
C4, C5: 6p; C0603K
C7: 100n; C0603K
C16: 0.1u; 0603-CAP
C19: 10u; C1210
C20: 10n; C0805
C21: 10u; C1206
CN1: DCBARRELPTH; DCJACK_2MM_PTH
D1, D2: B140-13-F; SMA-DIODE
D3: DIODESMA; SMADIODE
F1: PTCSMD; PTC-1206
IC2: LM358D; SO08
L1: SRN6045
LED1: LEDCHIP-LED0805; CHIP-LED0805
Q1: MOSFET-PCHANNELSMD; SOT23-3
R1, R2: 22; 0603-RES
R3: 330; R0603
R4, R5: 2k2; R0603
R6, R7, R9, R10, R11: 10k; R0603
R8: 52.3k; R0603
S1: SWITCH; TACTILE_SWITCH_SMD
SJ1: SJ
SV1: FE10-1; FE10
U1: USD SOCKET; MICRO-SD-SOCKET-PP
U2: CY8C5XXX; TQFP-14X14-100
U3: M05X2-0.05-SMD; PINHD-2X5-0.05-SMD
U4: LMR12010; TSOT-6
U5: TLV702XX; SOT23-5
U6: EEPROM-I2CSMD; SO08
U7: MICROUSB; USB-MICROB
U$5: F16X2; FE16-2
U$9: GND_CONNECT; GNDCONNECT
Y1: XRCGB_XTAL; XRCGB-XTAL

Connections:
+3V3: C1.1, C2.1, C6.1, C8.1, C9.1, C11.1, C12.1, C13.1, C14.1, C17.1, C18.1, IC2.2 (-IN), R4.2, R5.2, R9.2, SJ1.2, SV1.3, SV1.8, U1.4 (VCC), U2.26 (VDDIO1), U2.37 (VDDD), U2.50 (VDDIO3), U2.65 (VDDA), U2.75 (VDDIO0), U2.88 (VDDD), U2.100 (VDDIO2), U3.P$1 (1), U5.4 (OUT), U5.5 (OUT), U6.8 (VCC)
+5V: C3.1, C16.1, C21.1, D2.A, IC2.8 (V+), L1.P$2 (2), Q1.2 (S), R8.2, SV1.9, U5.1 (IN), U5.3 (EN)
AGND: C8.2, C10.2, C11.2, U2.64 (VSSA), U$9.AGND
BOOST: C20.1, D2.C, U4.P$1 (BOOST)
CLKI: C4.1, U2.43 (P15_1_MXTLI), Y1.2
CLKO: C5.1, U2.42 (P15_0_MXTLO), Y1.1
D+: R1.1, U2.35 (P15_6_DP)
D+IN: R1.2, U7.D+
D-: R2.1, U2.36 (P15_7_DM)
D-IN: R2.2, U7.D-
DCIN: CN1.PWR, D3.A
DGND: C1.2, C2.2, C4.2, C5.2, C6.2, C9.2, C12.2, C13.2, C14.2, C15.2, U2.10 (VSSD), U2.12 (VSSD), U2.13 (VSSD), U2.14 (VSSD), U2.38 (VSSD), U2.66 (VSSD), U2.87 (VSSD), U$9.DGND
FB: R7.2, R8.1, U4.P$3 (FB)
GND: C3.2, C16.2, C17.2, C18.2, C19.2, C21.2, CN1.GND, CN1.GNDBREAK, D1.A, IC2.4 (V-), LED1.C, R7.1, R11.1, S1.1, SV1.1, SV1.2, SV1.7, U1.6 (GND), U1.GND1 (SHIELD), U1.GND3 (SHIELD), U3.P$3 (3), U3.P$5 (5), U3.P$7 (7), U3.P$9 (9), U4.P$2 (GND), U5.2 (GND), U6.1 (A0), U6.2 (A1), U6.3 (A2), U6.4 (VSS), U7.GND, U$9.GND (IN)
GPIO1: U2.44 (P3_0), U$5.2
GPIO2: U2.45 (P3_1), U$5.1
GPIO3: U2.46 (P3_2), U$5.4
GPIO4: U2.47 (P3_3), U$5.3
GPIO5: U2.48 (P3_4), U$5.6
GPIO6: U2.49 (P3_5), U$5.5
GPIO7: U2.51 (P3_6), U$5.8
GPIO8: U2.52 (P3_7), U$5.7
GPIO9: U2.55 (P15_2_KXTLO), U$5.10
GPIO10: U2.56 (P15_3_KXTLI), U$5.9
GPIO11: U2.69 (P4_0), U$5.12
GPIO12: U2.70 (P4_1), U$5.11
GPIO13: U2.80 (P4_2), U$5.14
GPIO14: U2.81 (P4_3), U$5.13
GPIO15: U2.82 (P4_4), U$5.16
GPIO16: U2.83 (P4_5), U$5.15
GPIO17: U2.71 (P0_0), U$5.18
GPIO18: U2.72 (P0_1), U$5.17
GPIO19: U2.73 (P0_2), U$5.20
GPIO20: U2.74 (P0_3), U$5.19
GPIO21: U2.76 (P0_4), U$5.22
GPIO22: U2.77 (P0_5), U$5.21
GPIO23: U2.78 (P0_6), U$5.24
GPIO24: U2.79 (P0_7), U$5.23
GPIO25: U2.84 (P4_6), U$5.26
GPIO26: U2.85 (P4_7), U$5.25
GPIO27: U2.89 (P6_0), U$5.28
GPIO28: U2.90 (P6_1), U$5.27
GPIO29: U2.91 (P6_2), U$5.30
GPIO30: U2.92 (P6_3), U$5.29
GPIO31: U2.93 (P15_4), U$5.32
GPIO32: U2.94 (P15_5), U$5.31
INDIN: C20.2, D1.C, L1.P$1 (1), U4.P$6 (SW)
unnamed: R3.2, U2.1 (P2_5)
unnamed: C10.1, U2.63 (VCCA)
unnamed: R6.2, U4.P$4 (EN)
unnamed: SJ1.1, U6.7 (WP)
unnamed: IC2.3 (+IN), R10.1, R11.2
unnamed: IC2.6 (-IN), IC2.7 (OUT), Q1.1 (G)
unnamed: IC2.1 (OUT), IC2.5 (+IN)
unnamed: LED1.A, R3.1
P1[5]: C7.1, R9.1, S1.3 (2), U2.25 (P1_5_NTRST)
SCL0: R4.1, SV1.5, U2.4 (P12_4_I2C0_SCL), U6.6 (SCL)
SDA0: R5.1, SV1.4, U2.5 (P12_5_I2C0_SDA), U6.5 (SDA)
SWDCK: U2.21 (P1_1_TCK_SWDCK), U3.P$4 (4)
SWDIO: U2.20 (P1_0_TMS_SWDIO), U3.P$2 (2)
SWV: U2.23 (P1_3_TDO_SWV), U3.P$6 (6)
TDI: U2.24 (P1_4_TDI), U3.P$8 (8)
USBVCC: F1.1, Q1.3 (D)
USD_CD: U1.CD1 (SHIELD), U1.CD2 (SHIELD), U2.9 (P6_7)
USD_CS: U1.2 (CS), U2.19 (P5_3)
USD_DI: U1.3 (DI), U2.18 (P5_2)
USD_DO: U1.7 (DO), U2.16 (P5_0)
USD_SCK: U1.5 (SCK), U2.17 (P5_1)
V+: C19.1, D3.C, R6.1, R10.2, SV1.10, U4.P$5 (VIN)
VBUS: F1.2, U7.VBUS (VCC)
VCCD: C15.1, U2.39 (VCCD), U2.86 (VCCD)
XRES: C7.2, SV1.6, U2.15 (!XRES!), U3.P$10 (10)

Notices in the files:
parts and their libraries:
SparkFun-DigitalIC: Licensing: CC v3.0 Share-Alike You are welcome to use this library for commercial purposes.
microbuilder: This work is placed in the public domain, and may be freely used for commercial and non-commercial work with the following conditions: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
